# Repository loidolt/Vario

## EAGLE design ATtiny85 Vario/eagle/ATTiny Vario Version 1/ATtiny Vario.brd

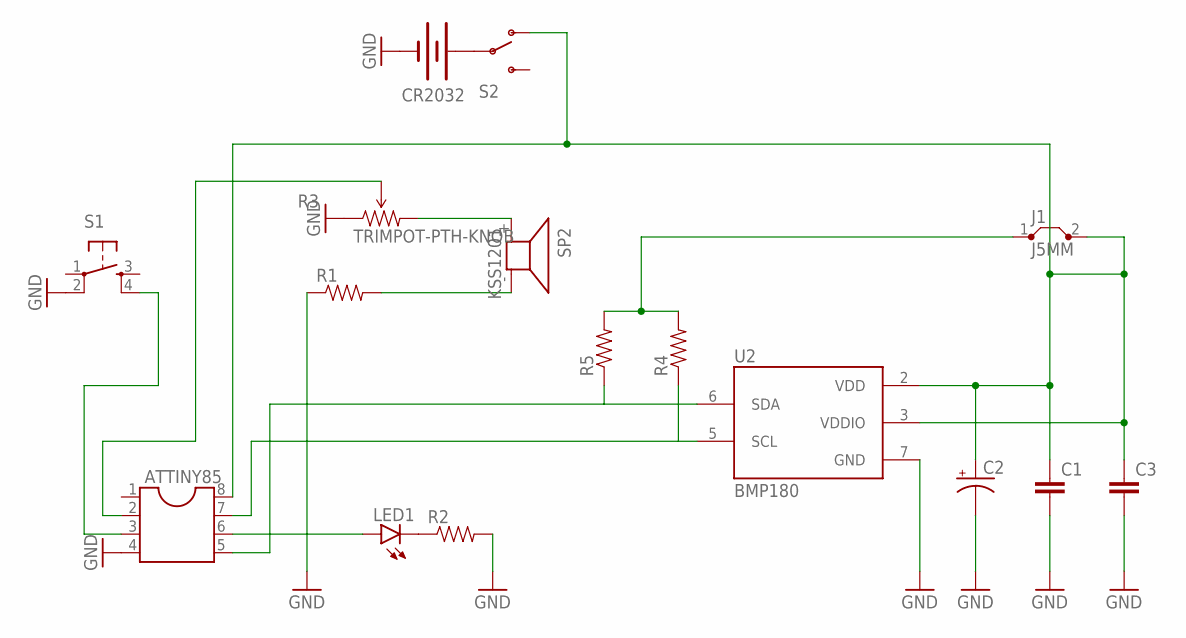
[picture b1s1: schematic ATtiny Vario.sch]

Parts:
ATTINY85: DIL8S; SOCKET-08
C1, C3: CAPPTH; CAP-PTH-SMALL
C2: CAP_POLPTH2; CPOL-RADIAL-10UF-25V
CR2032: BATTERY20PTH; BATTCOM_20MM_PTH
J1: J5MM; 05
LED1: LED3MM
R1, R4, R5: RESISTOREZ; AXIAL-0.3EZ
R2: RESISTORPTH-1/6W; 1/6W-RES
R3: TRIMPOT-PTH-KNOB; 3386U
S1: TAC_SWITCHPTH; TACTILE-PTH
S2: SWITCH-SPDTPTH; SWITCH-SPDT
SP2: KSS1201
U2: BMP180

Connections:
GND: ATTINY85.4, C1.2, C2.2 (-), C3.2, CR2032.2 (-), R1.P$1 (1), R2.2, R3.1 (CCW), S1.2, U2.7 (GND)
unnamed: CR2032.1 (+), S2.2
unnamed: ATTINY85.5, R5.P$1 (1), U2.6 (SDA)
unnamed: LED1.K (C), R2.1
unnamed: R1.P$2 (2), SP2.- (2)
unnamed: ATTINY85.8, C1.1, C2.1 (+), C3.1, J1.2, S2.1 (O), U2.2 (VDD), U2.3 (VDDIO)
unnamed: R3.3 (CW), SP2.+ (1)
unnamed: ATTINY85.2, R3.2 (WIPER)
unnamed: ATTINY85.3, S1.4
unnamed: ATTINY85.6, LED1.A
unnamed: J1.1, R4.P$2 (2), R5.P$2 (2)
unnamed: ATTINY85.7, R4.P$1 (1), U2.5 (SCL)

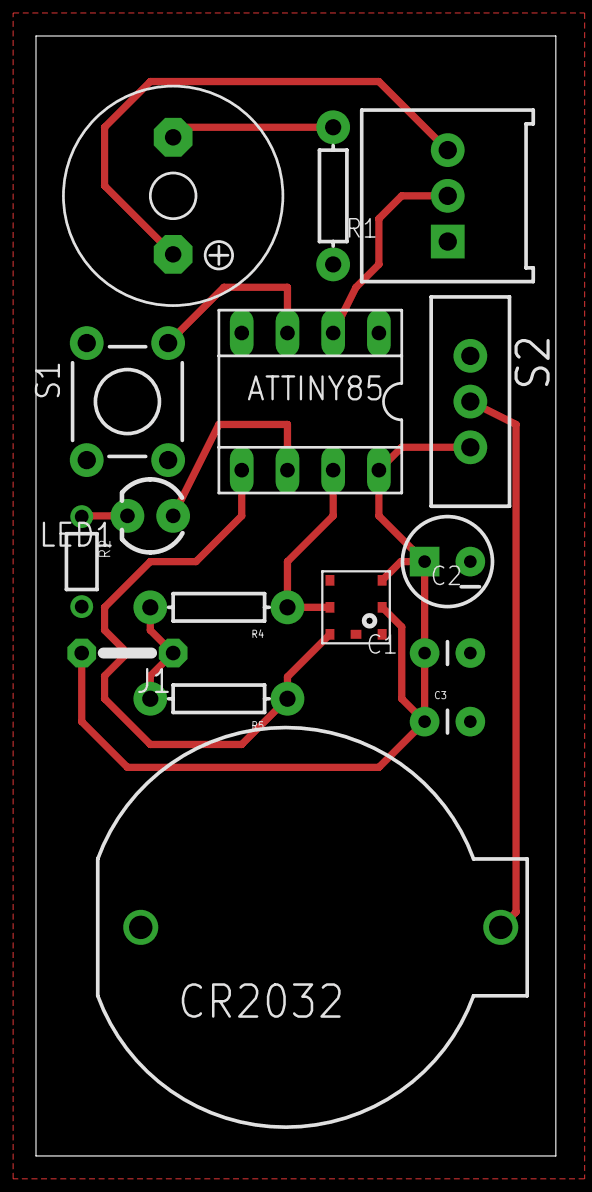
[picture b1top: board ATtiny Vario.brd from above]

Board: 2 copper layers, 28.9 x 62.2 mm, 16 parts (0 on the bottom side), 12 nets.

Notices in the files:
parts and their libraries:
SparkFun-Electromechanical: Licensing: Creative Commons ShareAlike 4.0 International - https://creativecommons.org/licenses/by-sa/4.0
